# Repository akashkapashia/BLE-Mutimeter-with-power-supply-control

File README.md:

# BLE-Mutimeter-with-power-supply-control
SPBTLE-1S(BLE Soc) Based multimeter with Serial display, PWM outputs for the power supply controls , voltage and current sense and UART as a host control interface.

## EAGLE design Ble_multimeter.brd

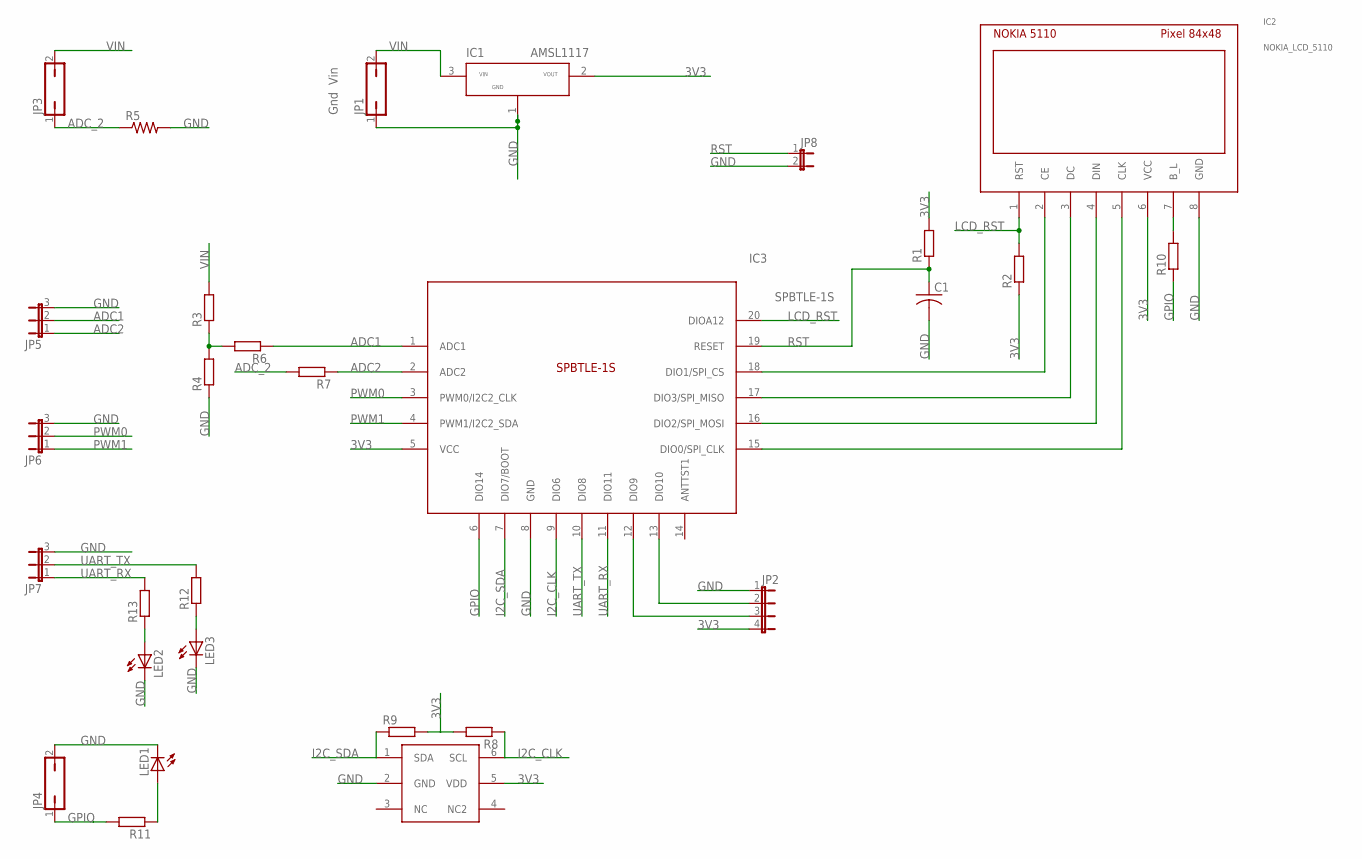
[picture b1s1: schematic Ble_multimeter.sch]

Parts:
C1: C-USC0805; C0805
IC1: AMSL1117; SOT223
IC2: NOKIA_LCD_5110; NOKIA_LCD_5110_8PIN
IC3: SPBTLE-1S; SPBTLE-1S_SMD20
IC4: HDC1080; 6_PIN_PWSON
JP1, JP3, JP4: JP1Q; JP1
JP2: JP4E; JP4
JP5, JP6, JP7: JP2E; JP2
JP8: JP1E; JP1
LED1, LED2, LED3: LED_E; LED_1206
R1, R2, R3, R4, R6, R7, R8, R9, R10, R11, R12, R13: R-EU_M1206; M1206
R5: R-US_0414/5V; 0414V

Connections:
3V3: IC1.2, IC2.6 (VCC), IC3.5 (VCC), IC4.5 (VDD), JP2.4, R1.2, R2.1, R8.2, R9.2
ADC1: IC3.1 (ADC1), JP5.2, R6.1
ADC2: IC3.2 (ADC2), JP5.1, R7.1
ADC_2: JP3.1, R5.1, R7.2
GND: C1.2, IC1.1, IC2.8 (GND), IC3.8 (GND), IC4.2 (GND), JP1.1, JP2.1, JP4.2, JP5.3, JP6.3, JP7.3, JP8.2, LED1.C, LED2.C, LED3.C, R4.1, R5.2
GPIO: IC3.6 (DIO14), JP4.1, R10.1, R11.2
I2C_CLK: IC3.9 (DIO6), IC4.6 (SCL), R8.1
I2C_SDA: IC3.7 (DIO7/BOOT), IC4.1 (SDA), R9.1
LCD_RST: IC2.1 (RST), IC3.20 (DIOA12), R2.2
unnamed: IC2.2 (CE), IC3.18 (DIO1/SPI_CS)
unnamed: IC2.4 (DIN), IC3.16 (DIO2/SPI_MOSI)
unnamed: IC2.5 (CLK), IC3.15 (DIO0/SPI_CLK)
unnamed: IC2.7 (B_L), R10.2
unnamed: IC2.3 (DC), IC3.17 (DIO3/SPI_MISO)
unnamed: IC3.13 (DIO10), JP2.2
unnamed: IC3.12 (DIO9), JP2.3
unnamed: R3.1, R4.2, R6.2
unnamed: LED3.A, R12.1
unnamed: LED2.A, R13.1
unnamed: LED1.A, R11.1
PWM0: IC3.3 (PWM0/I2C2_CLK), JP6.2
PWM1: IC3.4 (PWM1/I2C2_SDA), JP6.1
RST: C1.1, IC3.19 (RESET), JP8.1, R1.1
UART_RX: IC3.11 (DIO11), JP7.1, R13.2
UART_TX: IC3.10 (DIO8), JP7.2, R12.2
VIN: IC1.3, JP1.2, JP3.2, R3.2

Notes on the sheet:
Gnd Vin

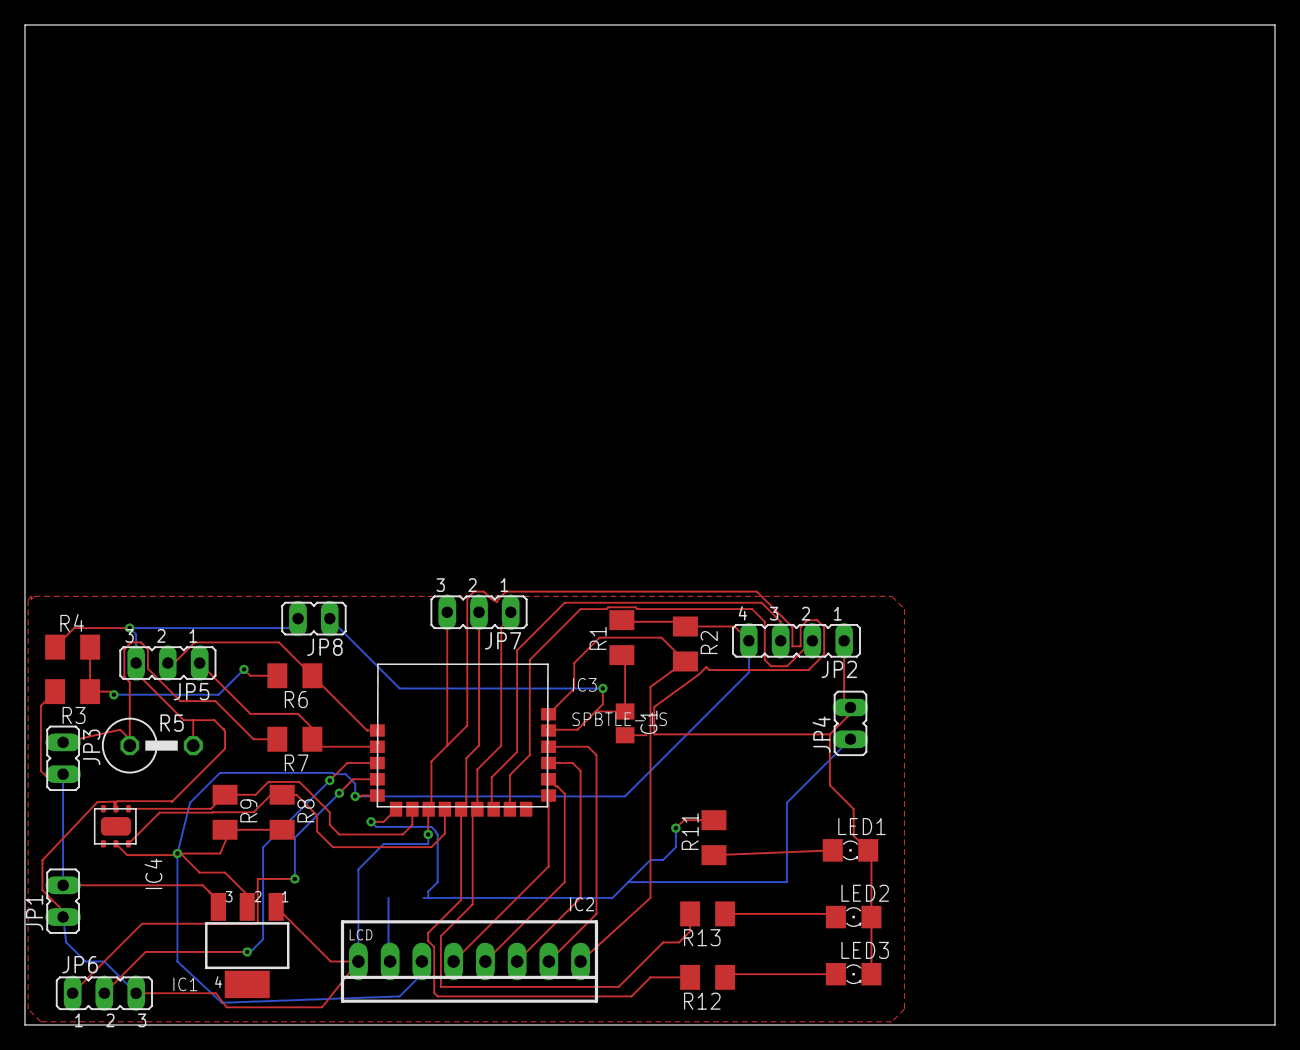
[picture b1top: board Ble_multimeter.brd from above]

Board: 2 copper layers, 100.0 x 80.0 mm, 29 parts (1 on the bottom side), 26 nets.
